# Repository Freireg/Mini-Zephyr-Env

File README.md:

# Mini-Zephyr-Env
This is a quick Zephyr project with a custom breakout board

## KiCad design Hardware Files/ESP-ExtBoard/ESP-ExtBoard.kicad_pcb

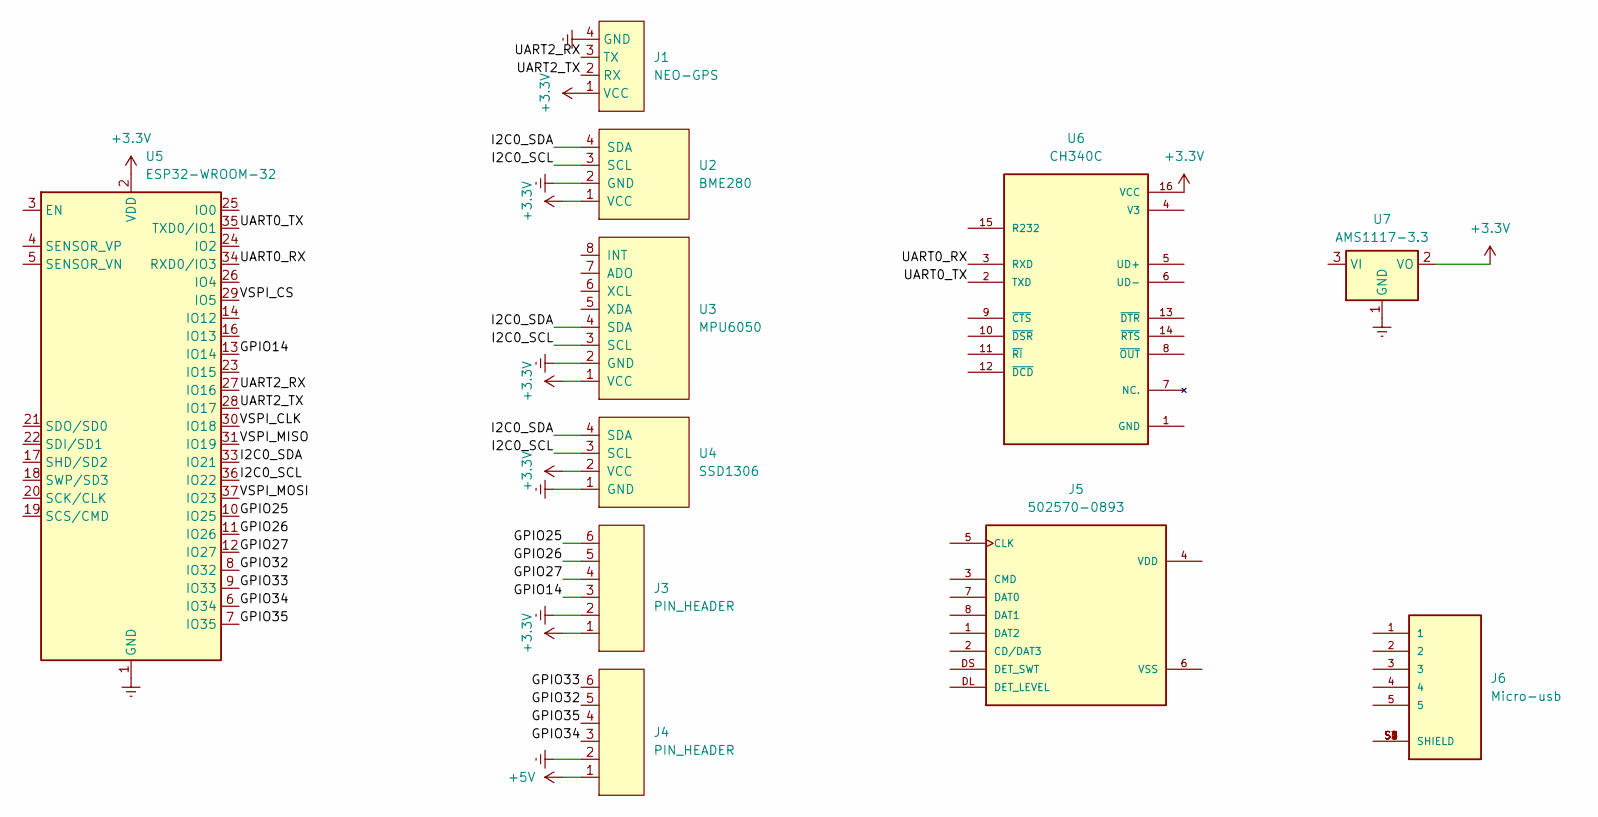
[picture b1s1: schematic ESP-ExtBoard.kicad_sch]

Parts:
J1: NEO-GPS
J3, J4: PIN_HEADER; PinHeader_1x06_P2.54mm_Vertical
J5: 502570-0893; MOLEX_502570-0893
J6: Micro-usb; AMPHENOL_10118194-0001LF; PARTREV D
U2: BME280; PinHeader_1x04_P2.54mm_Vertical
U3: MPU6050; PinHeader_1x08_P2.54mm_Vertical
U4: SSD1306; 128x64OLED
U5: ESP32-WROOM-32
U6: CH340C; SOIC127P600X180-16N; PARTREV 2G
U7: AMS1117-3.3; SOT-223-3_TabPin2

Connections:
+3.3V: J1.1 (VCC), J3.1, U2.1 (VCC), U3.1 (VCC), U4.2 (VCC), U5.2 (VDD), U6.16 (VCC), U7.2 (VO)
+5V: J4.1
/GPIO14: J3.3, U5.13 (IO14)
/GPIO25: J3.6, U5.10 (IO25)
/GPIO26: J3.5, U5.11 (IO26)
/GPIO27: J3.4, U5.12 (IO27)
/GPIO32: J4.5, U5.8 (IO32)
/GPIO33: J4.6, U5.9 (IO33)
/GPIO34: J4.3, U5.6 (IO34)
/GPIO35: J4.4, U5.7 (IO35)
/I2C0_SCL: U2.3 (SCL), U3.3 (SCL), U4.3 (SCL), U5.36 (IO22)
/I2C0_SDA: U2.4 (SDA), U3.4 (SDA), U4.4 (SDA), U5.33 (IO21)
/UART0_RX: U5.34 (RXD0/IO3), U6.3 (RXD)
/UART0_TX: U5.35 (TXD0/IO1), U6.2 (TXD)
/UART2_RX: J1.3 (TX), U5.27 (IO16)
/UART2_TX: J1.2 (RX), U5.28 (IO17)
/VSPI_CLK: U5.30 (IO18)
/VSPI_CS: U5.29 (IO5)
/VSPI_MISO: U5.31 (IO19)
/VSPI_MOSI: U5.37 (IO23)
Earth: J1.4 (GND), J3.2, J4.2, U2.2 (GND), U3.2 (GND), U4.1 (GND), U5.1 (GND), U5.15 (GND), U5.38 (GND), U5.39 (GND), U7.1 (GND)
unnamed: J6.S1 (SHIELD), J6.S2 (SHIELD), J6.S3 (SHIELD), J6.S4 (SHIELD), J6.S5 (SHIELD), J6.S6 (SHIELD)

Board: 2 copper layers, 11 parts (3 on the bottom side), 17 nets, no tracks yet.

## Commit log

2023-07-11 [firmware] First shell command
2023-07-12 minor tweaks on the repo organization
2023-07-12 Changing arch
2023-07-16 [hardware] Adding the PCB project
2023-07-16 Starting V2.0
2023-08-23 Basic queue implementation
2023-08-23 Msg queue usage
2023-08-24 Events notification implementation
2023-09-08 Inverted display colors
2023-09-09 Included BME280 & changed some files name
2023-09-09 Added GPS Module
2023-09-12 Inverted the OLED orientation
2023-09-12 Test command
2023-09-20 BTHome integration
2023-11-14 BLE central just connecting
